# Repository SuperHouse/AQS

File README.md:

Air Quality Sensor
==================

Build a DIY Air Quality Sensor to monitor the condition of the air in
your home or office, with options for measuring airborne particulate
matter, temperature, humidity, barometric pressure, and volatile
organic compounds.

This project is documented in an ongoing video series on SuperHouse:

* [DIY Air Quality Sensor, part 1: “Basic” version](https://www.superhouse.tv/38-diy-air-quality-sensor-part-1-basic-model/)
* [DIY Air Quality Sensor, part 2: “Display” version](https://www.superhouse.tv/39-diy-air-quality-sensor-part-2-display-version/)
* [DIY Air Quality Sensor, part 3: source code walkthrough](https://www.superhouse.tv/40-diy-air-quality-sensor-part-3-software/)

There are 3 different versions of this project:

 * The "Basic" version which requires only a Wemos D1 Mini and a
   Plantower PMS5003 laser particulate matter sensor.
 * The "Display" version which adds a 128x32 OLED display to the
   Basic version.
 * The "Pro" version which is based on a fully custom PCB with an ESP32
   MCU, a Plantower PMS7003 sensor, a Bosch BME680 environmental
   sensor, and a 240x240 colour LCD.

Measurements can be shown locally if a display is fitted, and can also
be reported to MQTT over WiFi so that data can be accessed by a home
automation system or external database.

"Basic" and "Display" version features:

 * PMS5003 particulate matter sensor
 * ESP8266 processor with WiFi
 * Micro-USB connection for power or reflashing
 * 3D-printable case

"Pro" version features:

 * PMS7003 particulate matter sensor
 * BME680 VOC sensor
 * ESP32 processor with WiFi and Bluetooth
 * USB-C connection for power or reflashing
 * 3D-printable case

More information is available at:

  https://www.superhouse.tv/aqs

Hardware
--------
The "Hardware" directory contains the PCB design as an EAGLE project.

Firmware
--------
The "Firmware" directory contains example firmware as an Arduino
project.

Enclosure
---------
The "Enclosure" directory contains STLs for a case that can be
3D-printed.

The two halves of the case should be printed with the flat face down to
the printer bed.

The case can be held shut by M3 bolts.

Credits
-------
 * Jonathan Oxer <jon@oxer.com.au>

License
-------
Copyright 2020-2021 SuperHouse Automation Pty Ltd  www.superhouse.tv  

The hardware portion of this project is licensed under the TAPR Open
Hardware License (www.tapr.org/OHL). The "license" folder within this
repository contains a copy of this license in plain text format.

The software portion of this project is licensed under the Simplified
BSD License. The "licence" folder within this project contains a
copy of this license in plain text format.

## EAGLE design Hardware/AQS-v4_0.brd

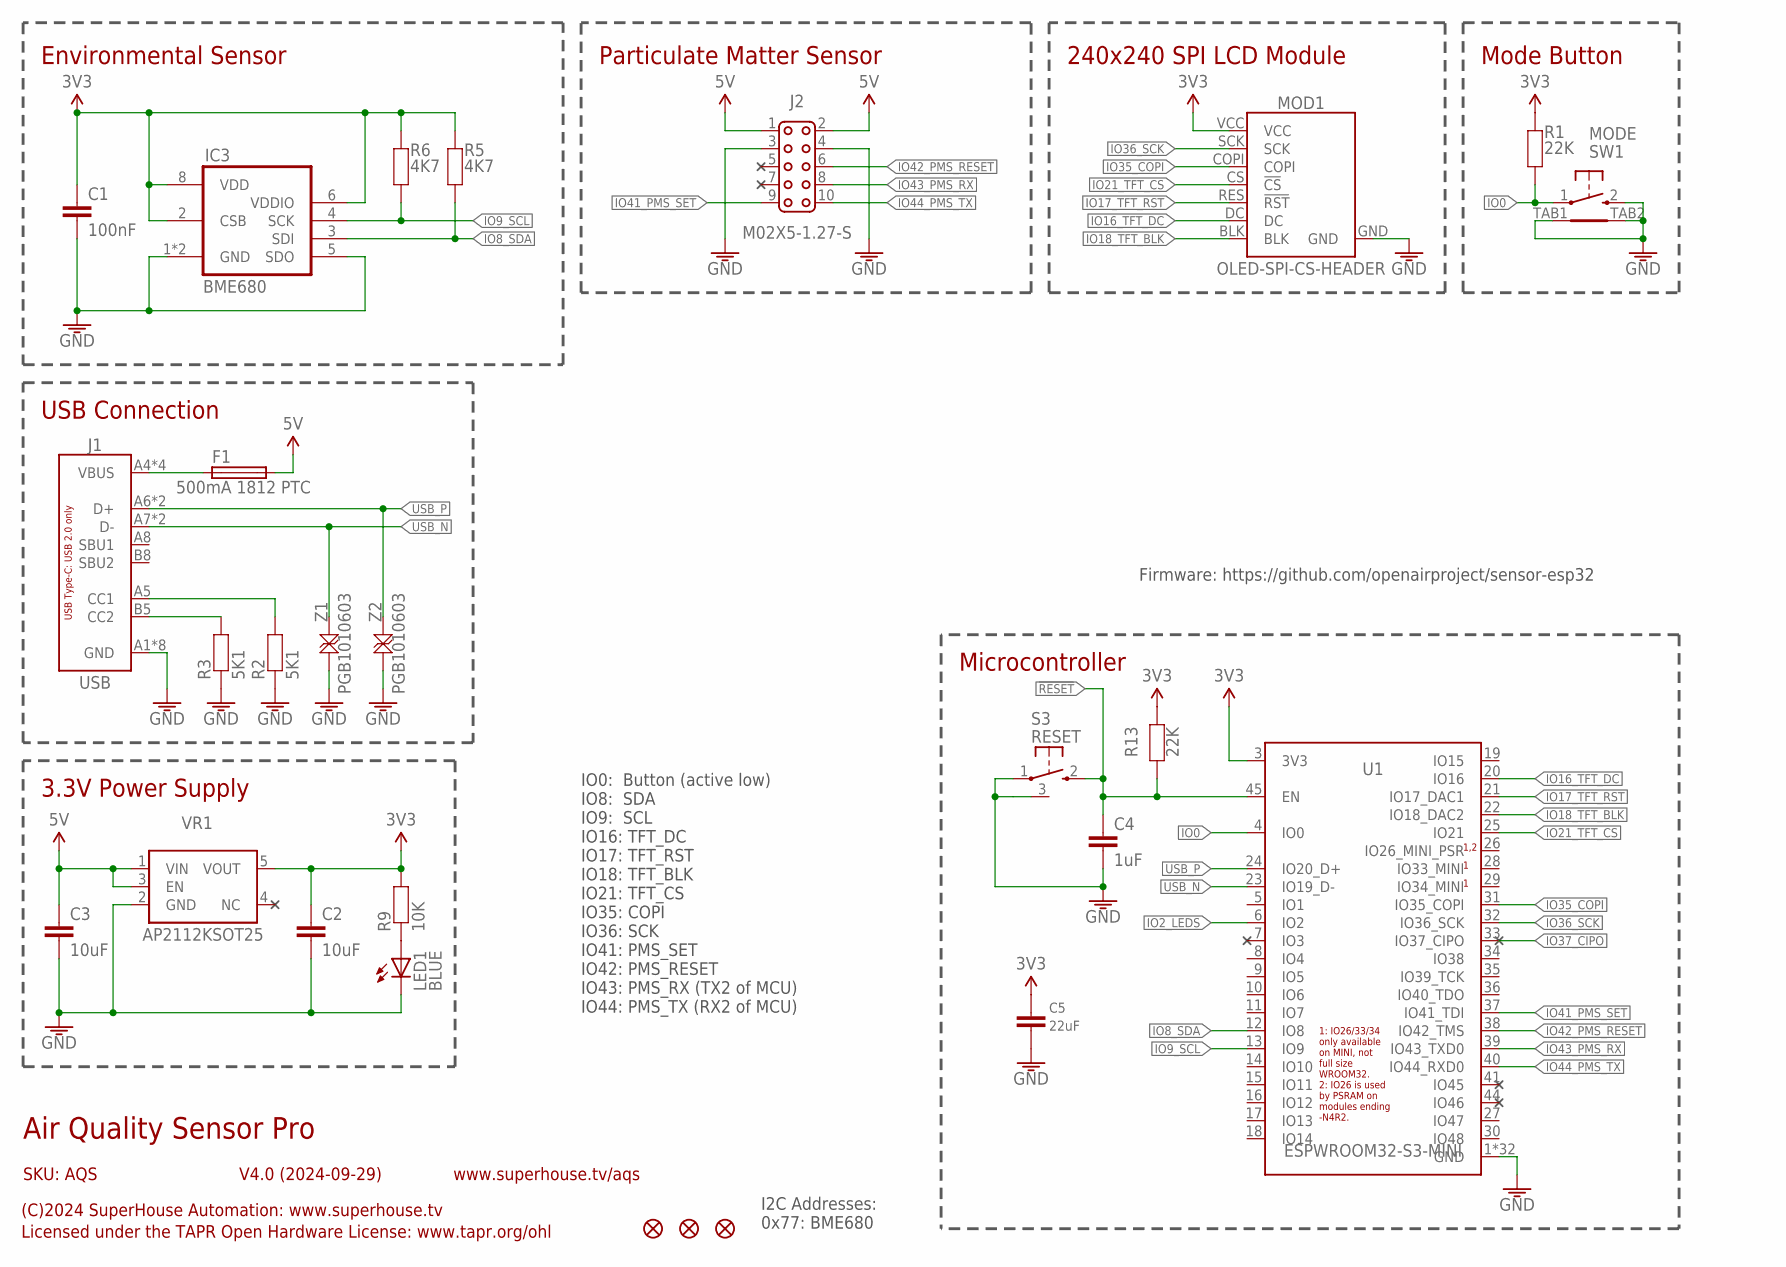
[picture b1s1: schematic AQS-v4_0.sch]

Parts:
C1: 100nF; C0603
C2, C3: 10uF; C0805
C4: 1uF; C0603
C5: 22uF; C0805
F1: 500mA 1812 PTC; 1206
IC3: BME680
J1: USB; USB-C-VERT
J2: M02X5-1.27-S; 2X05-1.27-S
LED1: BLUE; LED-0603
MOD1: OLED-SPI-CS-HEADER; OLED-240X240-1.54-HEADER
R1, R13: 22K; R0603
R2, R3: 5K1; R0603
R5, R6: 4K7; R0603
R9: 10K; R0603
S3: RESET; TACT-VERT-1TAB
SW1: MODE; TYCO-FSMRAJ
U1: ESPWROOM32-S3-MINI; ESP32-S3-MINI
U$23, U$24, U$25: FIDUCIAL1X2; FIDUCIAL-1X2
VR1: AP2112KSOT25; SOT23-5
Z1, Z2: PGB1010603; TVS0603

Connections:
3.3V: C1.1, C2.1, C5.1, IC3.2 (CSB), IC3.6 (VDDIO), IC3.8 (VDD), MOD1.VCC, R1.2, R5.2, R6.2, R9.2, R13.1, U1.3 (3V3), VR1.5 (VOUT)
5V: C3.1, F1.2, J2.1, J2.2, VR1.1 (VIN), VR1.3 (EN)
!RESET: C4.1, R13.2, S3.2, U1.45 (EN)
GND: C1.2, C2.2, C3.2, C4.2, C5.2, IC3.1 (GND), IC3.5 (SDO), IC3.7 (GND), J1.A1 (GND), J1.A12 (GND), J1.B1 (GND), J1.B12 (GND), J1.FIX1 (GND), J1.FIX2 (GND), J1.FIX3 (GND), J1.FIX4 (GND), J2.3, J2.4, LED1.C, MOD1.GND, R2.1, R3.1, S3.1, S3.3, SW1.2, SW1.TAB1, SW1.TAB2, U1.1 (GND), U1.2 (GND), U1.42 (GND), U1.43 (GND), U1.46 (GND), U1.47 (GND), U1.48 (GND), U1.49 (GND), U1.50 (GND), U1.51 (GND), U1.52 (GND), U1.53 (GND), U1.54 (GND), U1.55 (GND), U1.56 (GND), U1.57 (GND), U1.58 (GND), U1.59 (GND), U1.60 (GND), U1.61 (GND), U1.62 (GND), U1.63 (GND), U1.64 (GND), U1.65 (GND), U1.G1 (GND), U1.G2 (GND), U1.G3 (GND), U1.G4 (GND), U1.G6 (GND), U1.G7 (GND), U1.G8 (GND), U1.G9 (GND), VR1.2 (GND), Z1.1, Z2.1
IO0: R1.1, SW1.1, U1.4 (IO0)
IO2_LEDS: U1.6 (IO2)
IO8_SDA: IC3.3 (SDI), R5.1, U1.12 (IO8)
IO9_SCL: IC3.4 (SCK), R6.1, U1.13 (IO9)
IO16_TFT_DC: MOD1.DC, U1.20 (IO16)
IO17_TFT_RST: MOD1.RES (!RST), U1.21 (IO17_DAC1)
IO18_TFT_BLK: MOD1.BLK, U1.22 (IO18_DAC2)
IO21_TFT_CS: MOD1.CS (!CS), U1.25 (IO21)
IO35_COPI: MOD1.COPI, U1.31 (IO35_COPI)
IO36_SCK: MOD1.SCK, U1.32 (IO36_SCK)
IO37_CIPO: U1.33 (IO37_CIPO)
IO41_PMS_SET: J2.9, U1.37 (IO41_TDI)
IO42_PMS_RESET: J2.6, U1.38 (IO42_TMS)
IO43_PMS_RX: J2.8, U1.39 (IO43_TXD0)
IO44_PMS_TX: J2.10, U1.40 (IO44_RXD0)
IO46: U1.44 (IO46)
unnamed: LED1.A, R9.1
unnamed: F1.1, J1.A4 (VBUS), J1.A9 (VBUS), J1.B4 (VBUS), J1.B9 (VBUS)
unnamed: J1.B5 (CC2), R3.2
unnamed: J1.A5 (CC1), R2.2
USB_N: J1.A7 (D-), J1.B7 (D-), U1.23 (IO19_D-), Z1.2
USB_P: J1.A6 (D+), J1.B6 (D+), U1.24 (IO20_D+), Z2.2

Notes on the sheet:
V4.0 (2024-09-29)
USB Connection
3.3V Power Supply
Microcontroller
I2C Addresses: 0x77: BME680
IO0: Button (active low) IO8: SDA IO9: SCL IO16: TFT_DC IO17: TFT_RST IO18: TFT_BLK IO21: TFT_CS IO35: COPI IO36: SCK IO41: PMS_SET IO42: PMS_RESET IO43: PMS_RX (TX2 of MCU) IO44: PMS_TX (RX2 of MCU)
Air Quality Sensor Pro
SKU: AQS
(C)2024 SuperHouse Automation: www.superhouse.tv
Licensed under the TAPR Open Hardware License: www.tapr.org/ohl
www.superhouse.tv/aqs
Environmental Sensor
240x240 SPI LCD Module
Particulate Matter Sensor
Mode Button
Firmware: https://github.com/openairproject/sensor-esp32

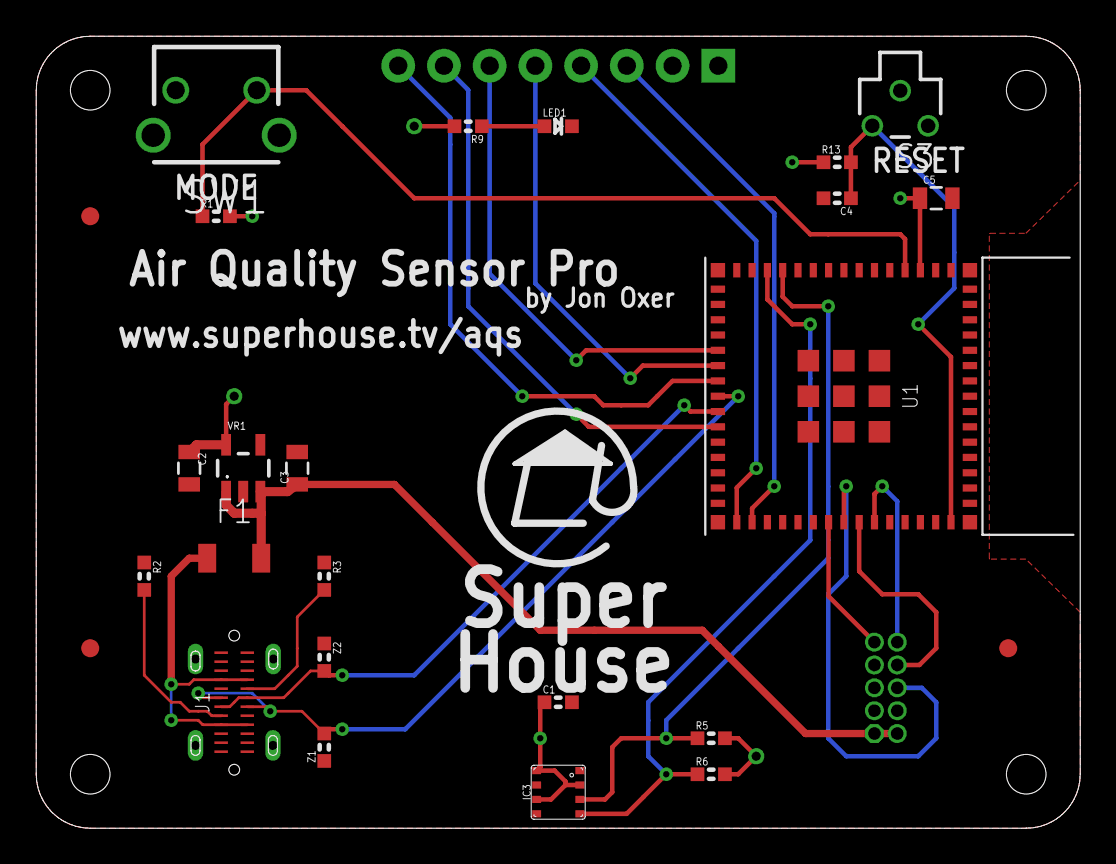
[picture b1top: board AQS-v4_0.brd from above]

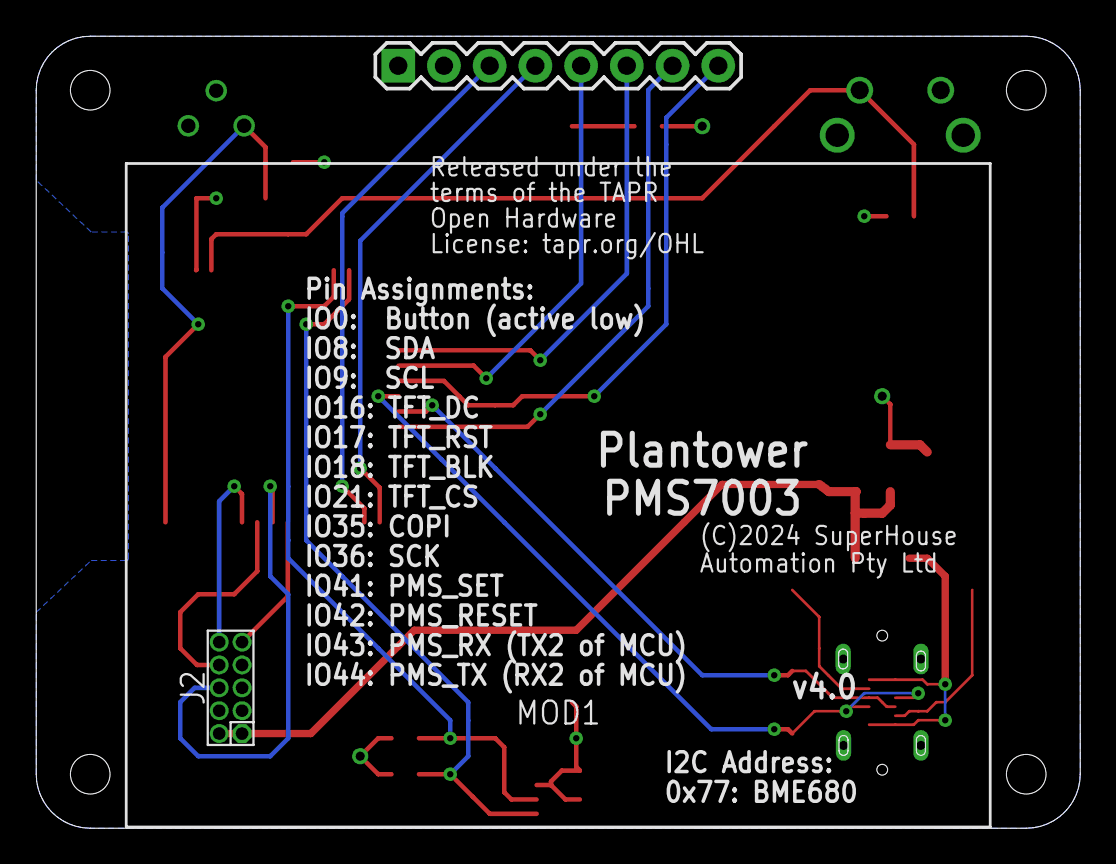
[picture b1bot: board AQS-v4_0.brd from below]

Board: 2 copper layers, 58.0 x 44.0 mm, 27 parts (2 on the bottom side), 23 nets.

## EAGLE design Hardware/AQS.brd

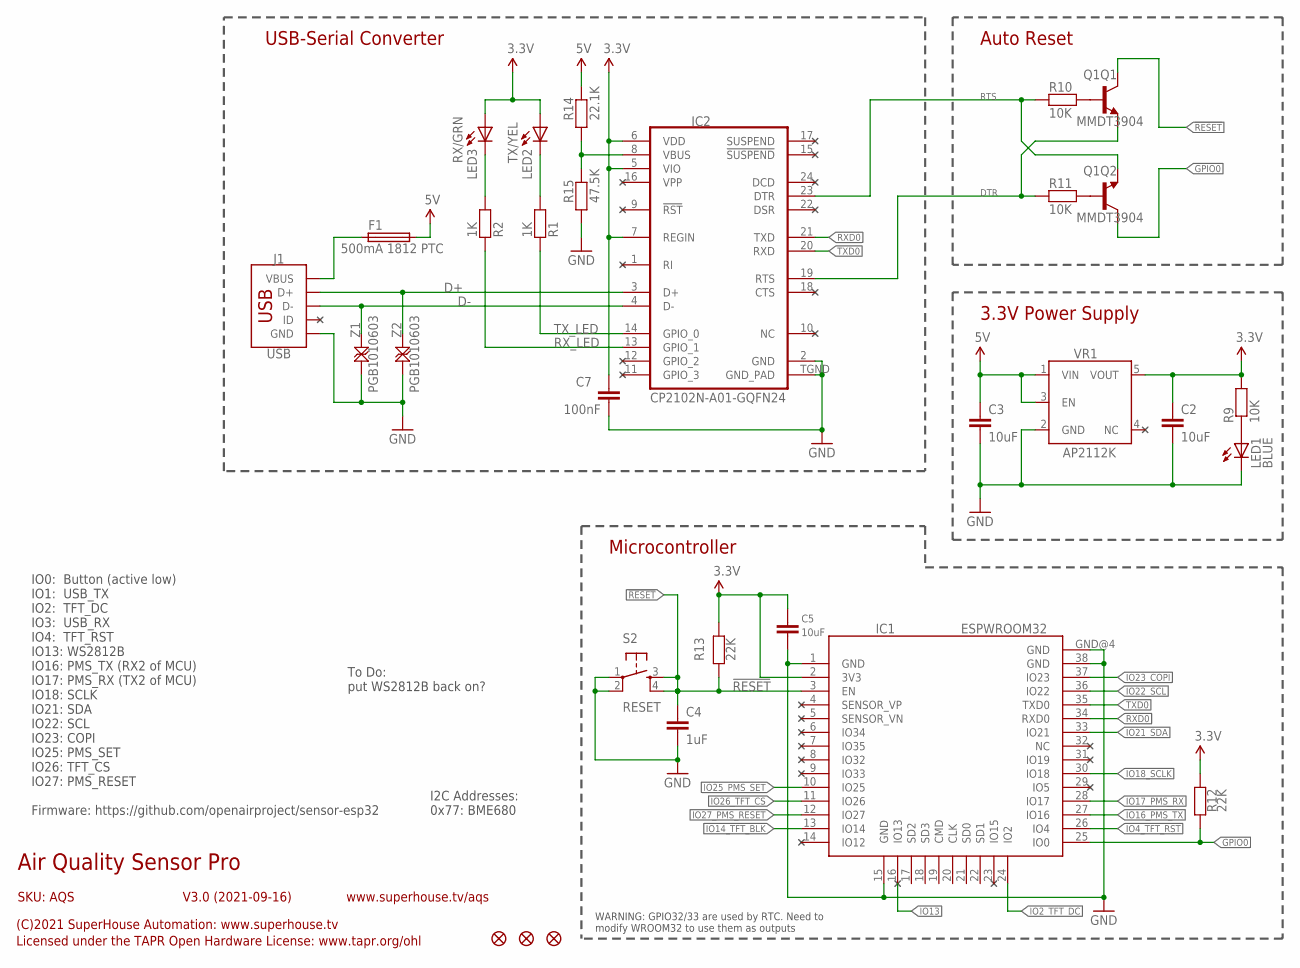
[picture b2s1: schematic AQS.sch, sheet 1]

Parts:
C2, C3, C5: 10uF; C0805
C4: 1uF; C0603
C7: 100nF; C0603
F1: 500mA 1812 PTC; 1206
IC1: ESPWROOM32
IC2: CP2102N-A01-GQFN24; QFN-24
J1: USB; USB-MICROB-VERT
LED1: BLUE; LED-0603
LED2: TX/YEL; LED-0603
LED3: RX/GRN; LED-0603
Q1: MMDT3904; SOT-363
R1, R2: 1K; R0603
R9, R10, R11: 10K; R0603
R12, R13: 22K; R0603
R14: 22.1K; R0603
R15: 47.5K; R0603
S2: RESET; TACTILE-PTH-4.5MM
U$23, U$24, U$25: FIDUCIAL1X2; FIDUCIAL-1X2
VR1: AP2112KSOT25; SOT23-5
Z1, Z2: PGB1010603; TVS0603

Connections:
3.3V: C2.1, C5.1, C7.1, IC1.2 (3V3), IC2.5 (VIO), IC2.6 (VDD), IC2.7 (REGIN), LED2.A, LED3.A, R9.2, R12.1, R13.1, VR1.5 (VOUT); also elsewhere on the board
5V: C3.1, F1.2, R14.2, VR1.1 (VIN), VR1.3 (EN); also elsewhere on the board
!RESET: C4.1, IC1.3 (EN), Q1.3 (C), R13.2, S2.3, S2.4
D+: IC2.3 (D+), J1.3 (D+), Z2.2
D-: IC2.4 (D-), J1.2 (D-), Z1.2
DTR: IC2.23 (DTR), Q1.1 (E), R10.1
GND: C2.2, C3.2, C4.2, C5.2, C7.2, IC1.1 (GND), IC1.15 (GND), IC1.38 (GND), IC1.GND@4 (GND), IC2.2 (GND), IC2.TGND (GND_PAD), J1.5 (GND), J1.POST1 (GND), J1.POST2 (GND), LED1.C, R15.1, S2.1, S2.2, VR1.2 (GND), Z1.1, Z2.1; also elsewhere on the board
GPIO0: IC1.25 (IO0), Q1.6 (C), R12.2; also elsewhere on the board
IO2_TFT_DC: IC1.24 (IO2); also elsewhere on the board
IO4_TFT_RST: IC1.26 (IO4); also elsewhere on the board
IO13: IC1.16 (IO13)
IO14_TFT_BLK: IC1.13 (IO14); also elsewhere on the board
IO16_PMS_TX: IC1.27 (IO16); also elsewhere on the board
IO17_PMS_RX: IC1.28 (IO17); also elsewhere on the board
IO18_SCLK: IC1.30 (IO18); also elsewhere on the board
IO21_SDA: IC1.33 (IO21); also elsewhere on the board
IO22_SCL: IC1.36 (IO22); also elsewhere on the board
IO23_COPI: IC1.37 (IO23); also elsewhere on the board
IO25_PMS_SET: IC1.10 (IO25); also elsewhere on the board
IO26_TFT_CS: IC1.11 (IO26); also elsewhere on the board
IO27_PMS_RESET: IC1.12 (IO27); also elsewhere on the board
unnamed: LED1.A, R9.1
unnamed: LED3.C, R2.2
unnamed: F1.1, J1.1 (VBUS)
unnamed: Q1.5 (B), R10.2
unnamed: Q1.2 (B), R11.2
unnamed: LED2.C, R1.2
unnamed: IC2.8 (VBUS), R14.1, R15.2
RTS: IC2.19 (RTS), Q1.4 (E), R11.1
RXD0: IC1.34 (RXD0), IC2.21 (TXD)
RX_LED: IC2.13 (GPIO_1), R2.1
TXD0: IC1.35 (TXD0), IC2.20 (RXD)
TX_LED: IC2.14 (GPIO_0), R1.1

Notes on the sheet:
V3.0 (2021-09-16)
USB-Serial Converter
Auto Reset
3.3V Power Supply
Microcontroller
WARNING: GPIO32/33 are used by RTC. Need to modify WROOM32 to use them as outputs
I2C Addresses: 0x77: BME680
IO0: Button (active low) IO1: USB_TX IO2: TFT_DC IO3: USB_RX IO4: TFT_RST IO13: WS2812B IO16: PMS_TX (RX2 of MCU) IO17: PMS_RX (TX2 of MCU) IO18: SCLK IO21: SDA IO22: SCL IO23: COPI IO25: PMS_SET IO26: TFT_CS IO27: PMS_RESET Firmware: https://github.com/openairproject/sensor-esp32
To Do: put WS2812B back on?
Air Quality Sensor Pro
SKU: AQS
(C)2021 SuperHouse Automation: www.superhouse.tv
Licensed under the TAPR Open Hardware License: www.tapr.org/ohl
www.superhouse.tv/aqs

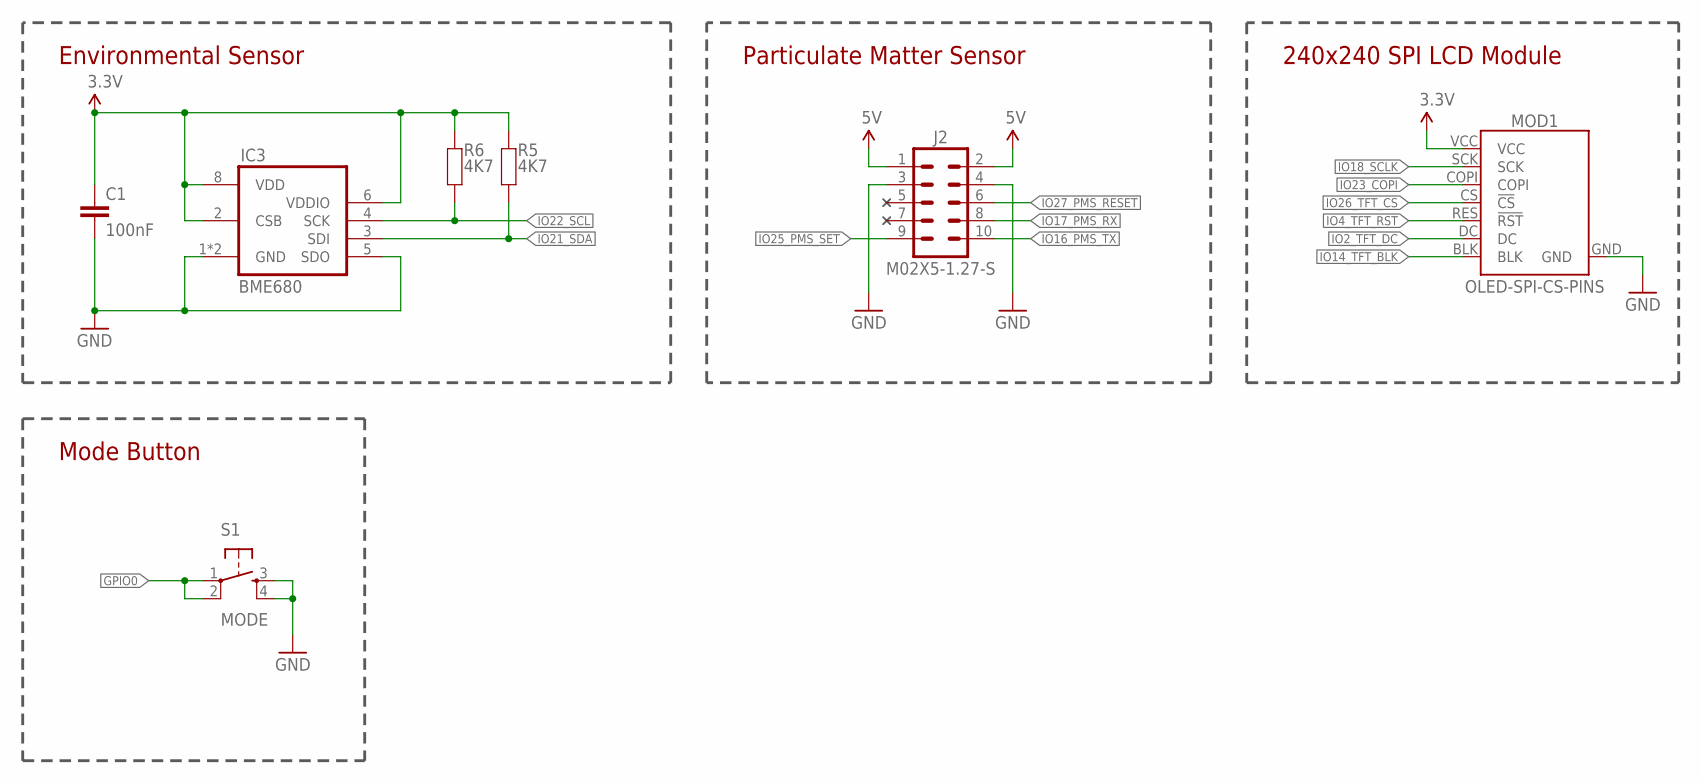
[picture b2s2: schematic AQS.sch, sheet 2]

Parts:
C1: 100nF; C0603
IC3: BME680
J2: M02X5-1.27-S; 2X05-1.27-S
MOD1: OLED-SPI-CS-PINS; OLED-240X240-1.54
R5, R6: 4K7; R0603
S1: MODE; TACTILE-PTH-4.5MM

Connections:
3.3V: C1.1, IC3.2 (CSB), IC3.6 (VDDIO), IC3.8 (VDD), MOD1.VCC, R5.2, R6.2; also elsewhere on the board
5V: J2.1, J2.2; also elsewhere on the board
GND: C1.2, IC3.1 (GND), IC3.5 (SDO), IC3.7 (GND), J2.3, J2.4, MOD1.GND, S1.3, S1.4; also elsewhere on the board
GPIO0: S1.1, S1.2; also elsewhere on the board
IO2_TFT_DC: MOD1.DC; also elsewhere on the board
IO4_TFT_RST: MOD1.RES (!RST); also elsewhere on the board
IO14_TFT_BLK: MOD1.BLK; also elsewhere on the board
IO16_PMS_TX: J2.10; also elsewhere on the board
IO17_PMS_RX: J2.8; also elsewhere on the board
IO18_SCLK: MOD1.SCK; also elsewhere on the board
IO21_SDA: IC3.3 (SDI), R5.1; also elsewhere on the board
IO22_SCL: IC3.4 (SCK), R6.1; also elsewhere on the board
IO23_COPI: MOD1.COPI; also elsewhere on the board
IO25_PMS_SET: J2.9; also elsewhere on the board
IO26_TFT_CS: MOD1.CS (!CS); also elsewhere on the board
IO27_PMS_RESET: J2.6; also elsewhere on the board

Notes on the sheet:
Environmental Sensor
240x240 SPI LCD Module
Particulate Matter Sensor
Mode Button

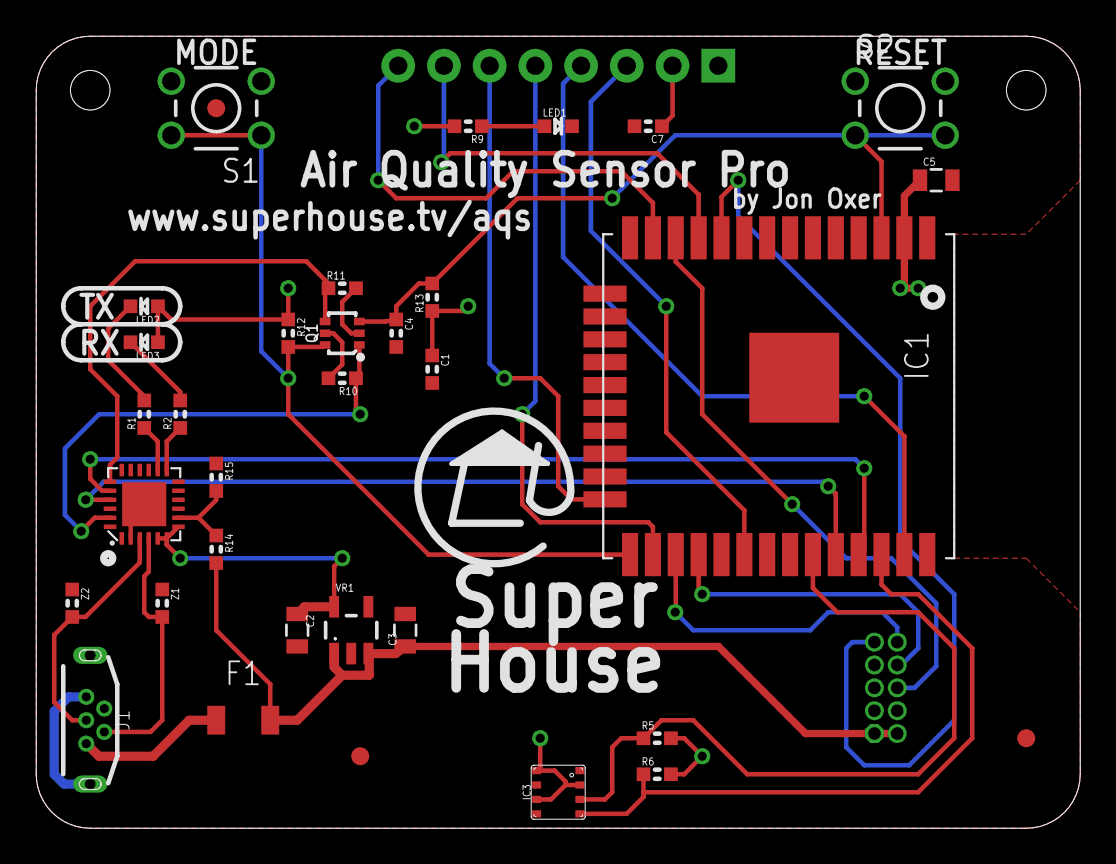
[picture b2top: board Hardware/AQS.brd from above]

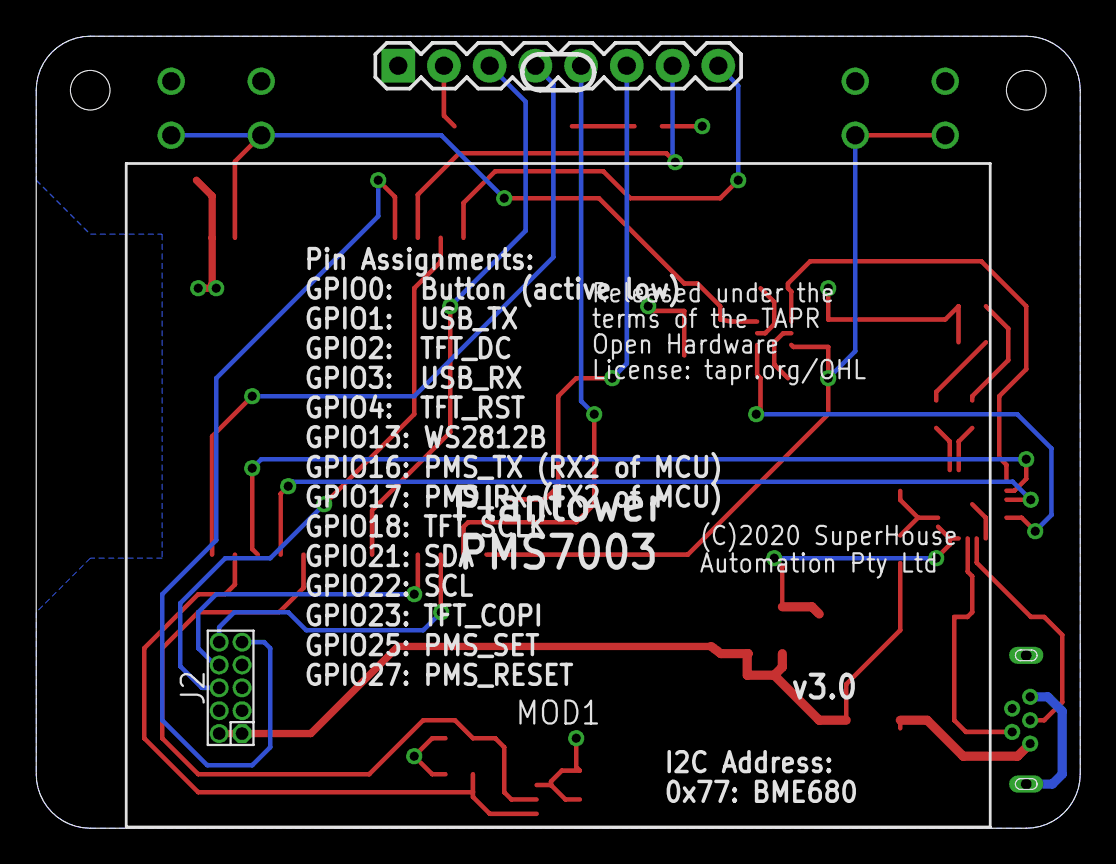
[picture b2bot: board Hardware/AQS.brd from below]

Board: 2 copper layers, 58.0 x 44.0 mm, 36 parts (2 on the bottom side), 32 nets.

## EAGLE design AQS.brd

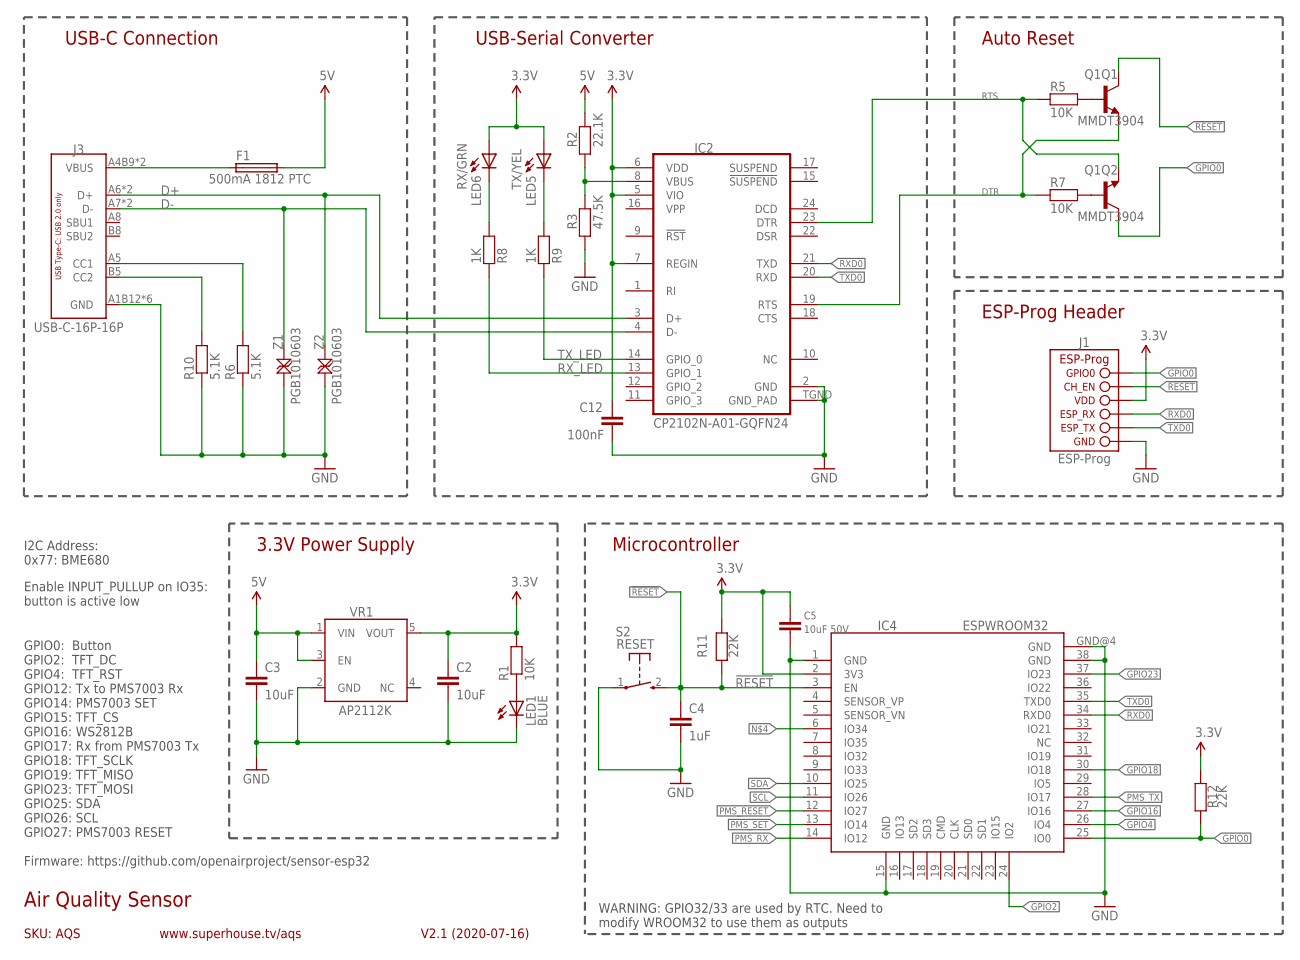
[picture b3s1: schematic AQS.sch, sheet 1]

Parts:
C2, C3: 10uF; C0603
C4: 1uF; C0603
C5: 10uF 50V; C0805
C12: 100nF; C0603
F1: 500mA 1812 PTC; 1812
IC2: CP2102N-A01-GQFN24; QFN-24
IC4: ESPWROOM32
J1: ESP-PROG-2X3-1.27-SHROUDED; 2X3-1.27-SHROUDED
J3: USB-C-16P-16P; USB-C-16P
LED1: BLUE; LED-0603
LED5: TX/YEL; LED-0603
LED6: RX/GRN; LED-0603
Q1: MMDT3904; SOT-363
R1, R5, R7: 10K; R0603
R2: 22.1K; R0603
R3: 47.5K; R0603
R6, R10: 5.1K; R0603
R8, R9: 1K; R0603
R11, R12: 22K; R0603
S2: RESET; TACTILE_SMT_3X4X2
VR1: AP2112KSOT25; SOT23-5
Z1, Z2: PGB1010603; TVS0603

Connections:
3.3V: C2.1, C5.1, C12.1, IC2.5 (VIO), IC2.6 (VDD), IC2.7 (REGIN), IC4.2 (3V3), J1.2 (VDD), LED5.A, LED6.A, R1.2, R11.1, R12.1, VR1.5 (VOUT); also elsewhere on the board
5V: C3.1, F1.2, R2.2, VR1.1 (VIN), VR1.3 (EN); also elsewhere on the board
!RESET: C4.1, IC4.3 (EN), J1.1 (CH_EN), Q1.3 (C), R11.2, S2.2 (S)
D+: IC2.3 (D+), J3.A6 (D+), J3.B6 (D+), Z2.2
D-: IC2.4 (D-), J3.A7 (D-), J3.B7 (D-), Z1.2
DTR: IC2.23 (DTR), Q1.1 (E), R5.1
GND: C2.2, C3.2, C4.2, C5.2, C12.2, IC2.2 (GND), IC2.TGND (GND_PAD), IC4.1 (GND), IC4.15 (GND), IC4.38 (GND), IC4.GND@4 (GND), J1.4 (GND), J3.A1B12 (GND), J3.A12B1 (GND), J3.FIX1 (GND), J3.FIX2 (GND), J3.FIX3 (GND), J3.FIX4 (GND), LED1.C, R3.1, R6.1, R10.1, S2.1, VR1.2 (GND), Z1.1, Z2.1; also elsewhere on the board
GPIO0: IC4.25 (IO0), J1.6 (GPIO0), Q1.6 (C), R12.2; also elsewhere on the board
GPIO2: IC4.24 (IO2); also elsewhere on the board
GPIO4: IC4.26 (IO4); also elsewhere on the board
GPIO16: IC4.27 (IO16); also elsewhere on the board
GPIO18: IC4.30 (IO18); also elsewhere on the board
GPIO23: IC4.37 (IO23); also elsewhere on the board
unnamed: LED1.A, R1.1
unnamed: LED6.C, R8.2
unnamed: Q1.5 (B), R5.2
unnamed: Q1.2 (B), R7.2
unnamed: J3.B5 (CC2), R10.2
unnamed: J3.A5 (CC1), R6.2
unnamed: LED5.C, R9.2
unnamed: IC2.8 (VBUS), R2.1, R3.2
PMS_RESET: IC4.12 (IO27); also elsewhere on the board
PMS_RX: IC4.14 (IO12); also elsewhere on the board
PMS_SET: IC4.13 (IO14); also elsewhere on the board
PMS_TX: IC4.28 (IO17); also elsewhere on the board
RTS: IC2.19 (RTS), Q1.4 (E), R7.1
RXD0: IC2.21 (TXD), IC4.34 (RXD0), J1.5 (ESP_RX)
RX_LED: IC2.13 (GPIO_1), R8.1
SCL: IC4.11 (IO26); also elsewhere on the board
SDA: IC4.10 (IO25); also elsewhere on the board
TXD0: IC2.20 (RXD), IC4.35 (TXD0), J1.3 (ESP_TX)
TX_LED: IC2.14 (GPIO_0), R9.1
VIN: F1.1, J3.A4B9 (VBUS), J3.A9B4 (VBUS)

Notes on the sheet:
SKU: AQS
Air Quality Sensor
V2.1 (2020-07-16)
www.superhouse.tv/aqs
USB-C Connection
USB-Serial Converter
Auto Reset
3.3V Power Supply
Microcontroller
WARNING: GPIO32/33 are used by RTC. Need to modify WROOM32 to use them as outputs
Enable INPUT_PULLUP on IO35: button is active low
GPIO0: Button GPIO2: TFT_DC GPIO4: TFT_RST GPIO12: Tx to PMS7003 Rx GPIO14: PMS7003 SET GPIO15: TFT_CS GPIO16: WS2812B GPIO17: Rx from PMS7003 Tx GPIO18: TFT_SCLK GPIO19: TFT_MISO GPIO23: TFT_MOSI GPIO25: SDA GPIO26: SCL GPIO27: PMS7003 RESET Firmware: https://github.com/openairproject/sensor-esp32
I2C Address: 0x77: BME680
ESP-Prog Header

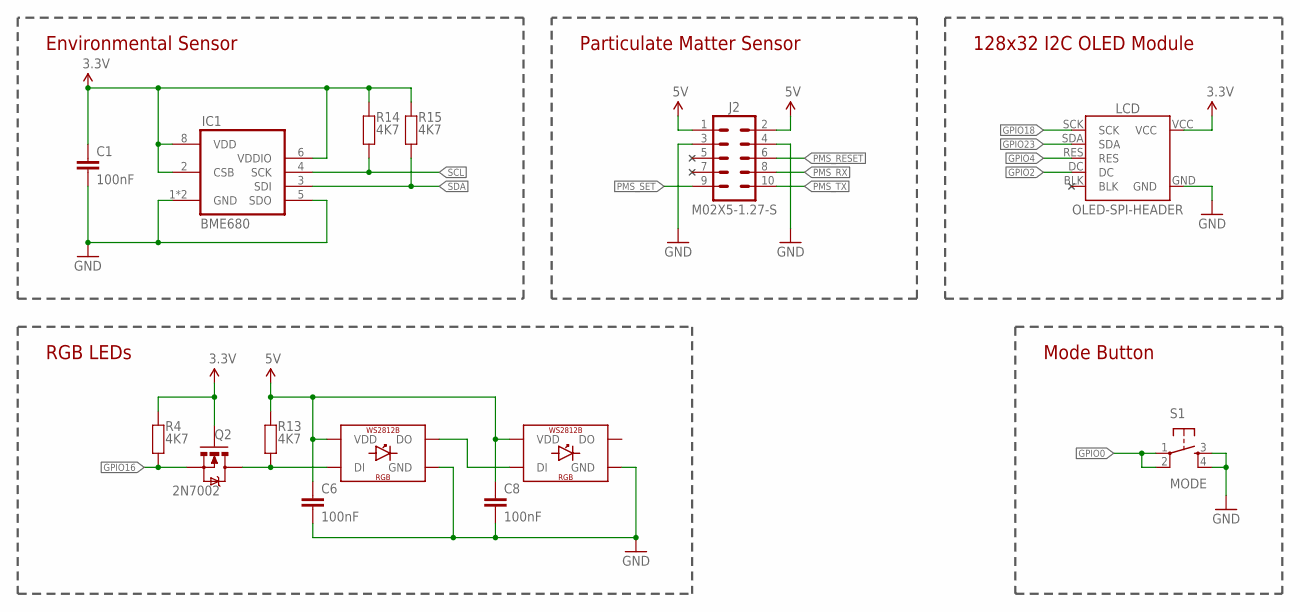
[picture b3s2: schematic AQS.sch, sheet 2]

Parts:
C1, C6, C8: 100nF; C0603
IC1: BME680
J2: M02X5-1.27-S; 2X05-1.27-S
LCD: OLED-SPI-HEADER; OLED-240X240-1.3-HEADER
LED2, LED4: WS2812B5050; WS2812B
Q2: 2N7002; SOT23-3
R4, R13, R14, R15: 4K7; R0603
S1: MODE; TACTILE-PTH-4.5MM

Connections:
3.3V: C1.1, IC1.2 (CSB), IC1.6 (VDDIO), IC1.8 (VDD), LCD.VCC, Q2.1 (G), R4.2, R14.2, R15.2; also elsewhere on the board
5V: C6.1, C8.1, J2.1, J2.2, LED2.1-VDD (VDD), LED4.1-VDD (VDD), R13.2; also elsewhere on the board
GND: C1.2, C6.2, C8.2, IC1.1 (GND), IC1.5 (SDO), IC1.7 (GND), J2.3, J2.4, LCD.GND, LED2.3-GND (GND), LED4.3-GND (GND), S1.3, S1.4; also elsewhere on the board
GPIO0: S1.1, S1.2; also elsewhere on the board
GPIO2: LCD.DC; also elsewhere on the board
GPIO4: LCD.RES; also elsewhere on the board
GPIO16: Q2.2 (S), R4.1; also elsewhere on the board
GPIO18: LCD.SCK; also elsewhere on the board
GPIO23: LCD.SDA; also elsewhere on the board
H1: LED2.4-DIN (DI), Q2.3 (D), R13.1
unnamed: LED2.2-DOUT (DO), LED4.4-DIN (DI)
PMS_RESET: J2.6; also elsewhere on the board
PMS_RX: J2.8; also elsewhere on the board
PMS_SET: J2.9; also elsewhere on the board
PMS_TX: J2.10; also elsewhere on the board
SCL: IC1.4 (SCK), R14.1; also elsewhere on the board
SDA: IC1.3 (SDI), R15.1; also elsewhere on the board

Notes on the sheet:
Environmental Sensor
128x32 I2C OLED Module
Particulate Matter Sensor
RGB LEDs
Mode Button

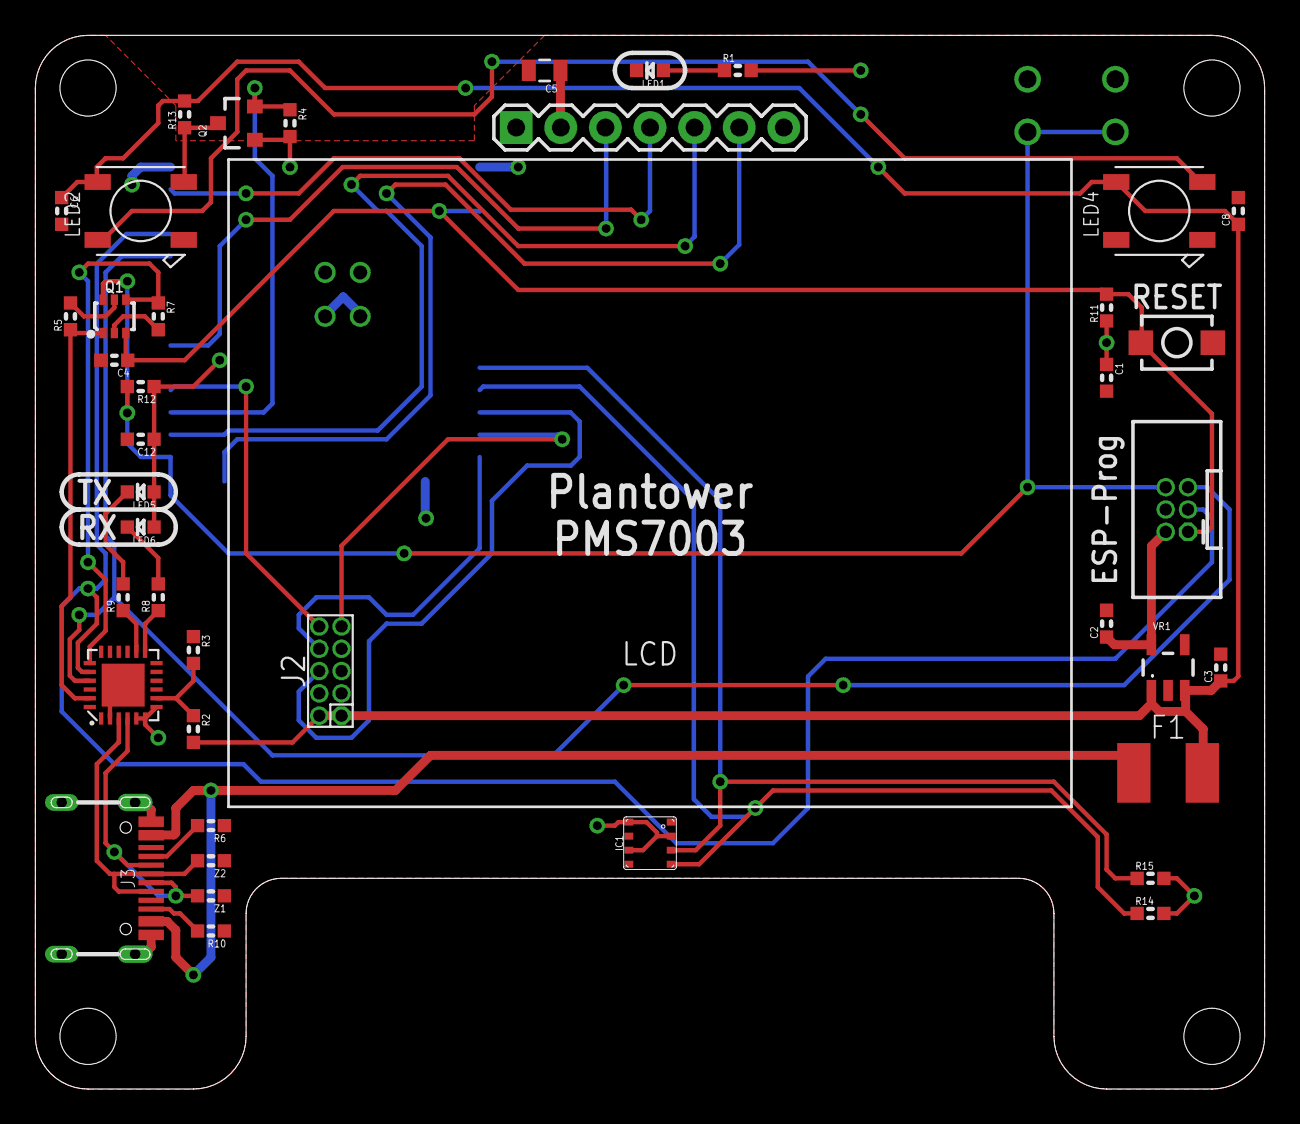
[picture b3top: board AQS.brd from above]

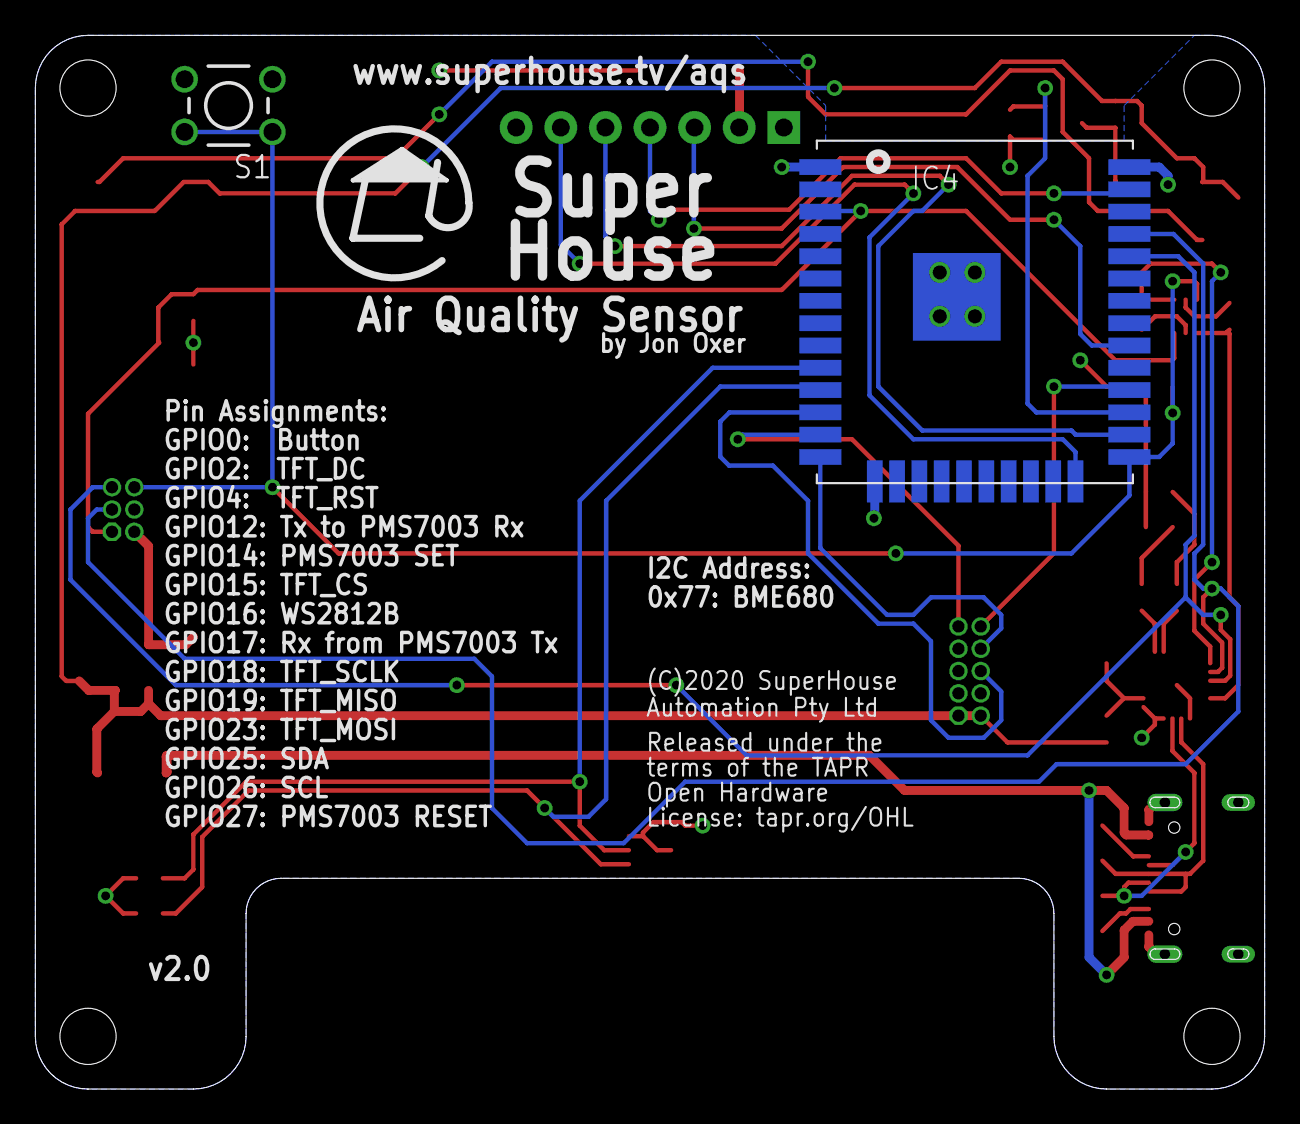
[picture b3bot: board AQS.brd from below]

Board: 2 copper layers, 70.0 x 60.0 mm, 43 parts (2 on the bottom side), 35 nets.

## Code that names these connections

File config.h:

/* ----------------- General Config -------------------------------- */
/* WiFi config */
const char* ssid                  = "YOUR SSID";     // Your WiFi SSID
const char* password              = "YOUR PASS";     // Your WiFi password

/* MQTT */
const char* mqtt_broker           = "192.168.1.111"; // IP address of your MQTT broker
#define     REPORT_MQTT_SEPARATE  true               // Report each value to its own topic
#define     REPORT_MQTT_JSON      true               // Report all values in a JSON message
const char* status_topic          = "events";        // MQTT topic to report startup

/* Particulate Matter Sensor */
uint32_t    g_pms_warmup_period   =  30;             // Seconds to warm up PMS before reading
uint32_t    g_pms_report_period   = 120;             // Seconds between reports

/* Use WiFi. If this is off, MQTT won't run */
#define ENABLE_WIFI       true

/* Serial */
#define     SERIAL_BAUD_RATE       9600              // Speed for USB serial console

/* Environmental sensor */
#define SEA_LEVEL_PRESSURE_HPA (1013.25)

/* ----------------- Hardware-specific Config ---------------------- */
/* Mode button connection (momentary between this pin and GND) */
#define MODE_BUTTON_PIN    0

/* RGB LEDs */
#define WS2812B_PIN       13
#define NUM_RGB_LEDS       2

/* LCD */
#define TFT_DC_PIN         2
#define TFT_RST_PIN        4
#define TFT_CS_PIN        26
#define TFT_SCLK_PIN      18
#define TFT_MISO_PIN      19
#define TFT_MOSI_PIN      23

/* I2C */
#define I2C_SDA_PIN       21
#define I2C_SCL_PIN       22
#define BME680_I2C_ADDR 0x76

/* Particulate Matter Sensor */
#define PMS_BAUD_RATE   9600
#define PMS_SET_PIN       25
#define PMS_RESET_PIN     27
#define PMS_RX_PIN        17 //  Tx to the PMS SHOULD BE 16
#define PMS_TX_PIN        16 //  Rx from the PMS SHOULD BE 17

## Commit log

2020-02-09 Initial import
2020-02-09 Added image
2020-02-10 Major update to use 240x240 SPI LCD
2020-02-10 Updated render
2020-02-14 Forked project from D1 Mini version
2020-02-14 Fixed button pin config
2020-02-14 Convert to ESP32, add LCD support, add SuperHouse logo, add serial port for PMS7003
2020-02-14 Display average and latest values on LCD
2020-02-17 Changed TX pin to PMS7003
2020-02-19 Major update: added BME680, refactored much code, separated config values
2020-03-04 Added I2C address for BME680. Changed name of reporting period option to match Tasmota convention. Added sea level pressure value for altitude calculations.
2020-03-04 Changed MQTT topic names to match Tasmota conventions. Major improvements to TFT screen formatting. Made sensor updates asynchronous to decouple it from reporting methods.
2020-03-08 Moved mode button to GPIO0
2020-04-30 Replaced CP2102N with CH340G; removed 2 LEDs; reworked routing; moved button
2020-06-15 Replaced programming header
2020-07-15 Routing for CP2102N
2020-07-15 Restructuring in preparation for merging projects
2020-07-15 Added license files
2020-07-16 Added SimplicityStudio profile for CP2012N
2020-07-16 Major restructure and changes to pin allocations
2020-07-16 Moved example firmware into subdirectory
2020-07-17 Finished major rework for v3.0 release
2020-08-09 Report MQTT parameters via serial port
2020-08-09 Experiments with alternative layout putting all SMT parts behind the sensor to reduce size
2021-04-22 Added design files for enclosures.
2021-04-22 Added images of different versions and enclosures.
2021-04-22 Added .gitignore.
2021-04-22 Merged in firmware for Basic and Display versions.
2021-04-22 Added -local files to .gitignore.
2021-04-23 Updated README to mention all 3 versions of the project.
2021-04-23 Added links to videos.
2021-04-23 Added brief README. Needs to be expanded.
2021-05-08 Switched PMS libraries
2021-05-30 Add config for PlatformIO
2021-06-03 Fix button logic
    Without the patch the display keeps switching the state fast until you release
    the button.
2021-09-26 Major restructure to reduce size of PCB. ERC and DRC for v3.0 release.
2021-09-26 Removed extra board layers.
2021-09-26 Cleanup Mac files.
2024-01-15 Added STEP files.
2024-10-03 Updated hardware files for v4.0 release.
2024-10-03 Deleted obsolete files.

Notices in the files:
AQS.brd:
(C)2020 SuperHouse
License: tapr.org/OHL
parts and their libraries:
freetronics-original: Licensing: CC v3.0 Share-Alike You are welcome to use this library for commercial purposes.
